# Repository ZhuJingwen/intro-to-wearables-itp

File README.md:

# intro-to-wearables-itp
A repository of examples for the class Intro to Wearables.

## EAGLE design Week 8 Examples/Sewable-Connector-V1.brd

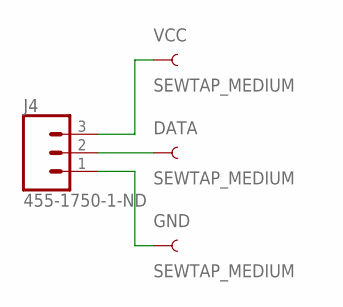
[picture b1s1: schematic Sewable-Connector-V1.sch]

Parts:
DATA: SEWTAP_MEDIUM; PETAL-MEDIUM
GND: SEWTAP_MEDIUM; PETAL-MEDIUM
J4: 455-1750-1-ND; 1X03
VCC: SEWTAP_MEDIUM; PETAL-MEDIUM

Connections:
unnamed: J4.3, VCC.1
unnamed: DATA.1, J4.2
unnamed: GND.1, J4.1

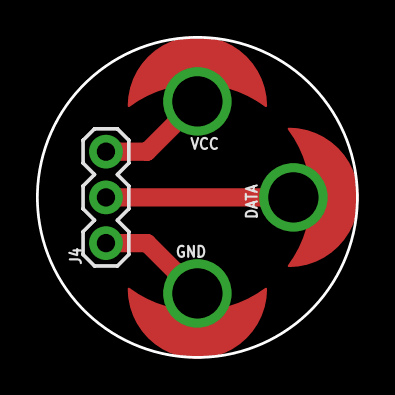
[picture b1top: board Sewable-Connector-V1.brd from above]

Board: 2 copper layers, 17.8 x 17.8 mm, 4 parts (0 on the bottom side), 3 nets.

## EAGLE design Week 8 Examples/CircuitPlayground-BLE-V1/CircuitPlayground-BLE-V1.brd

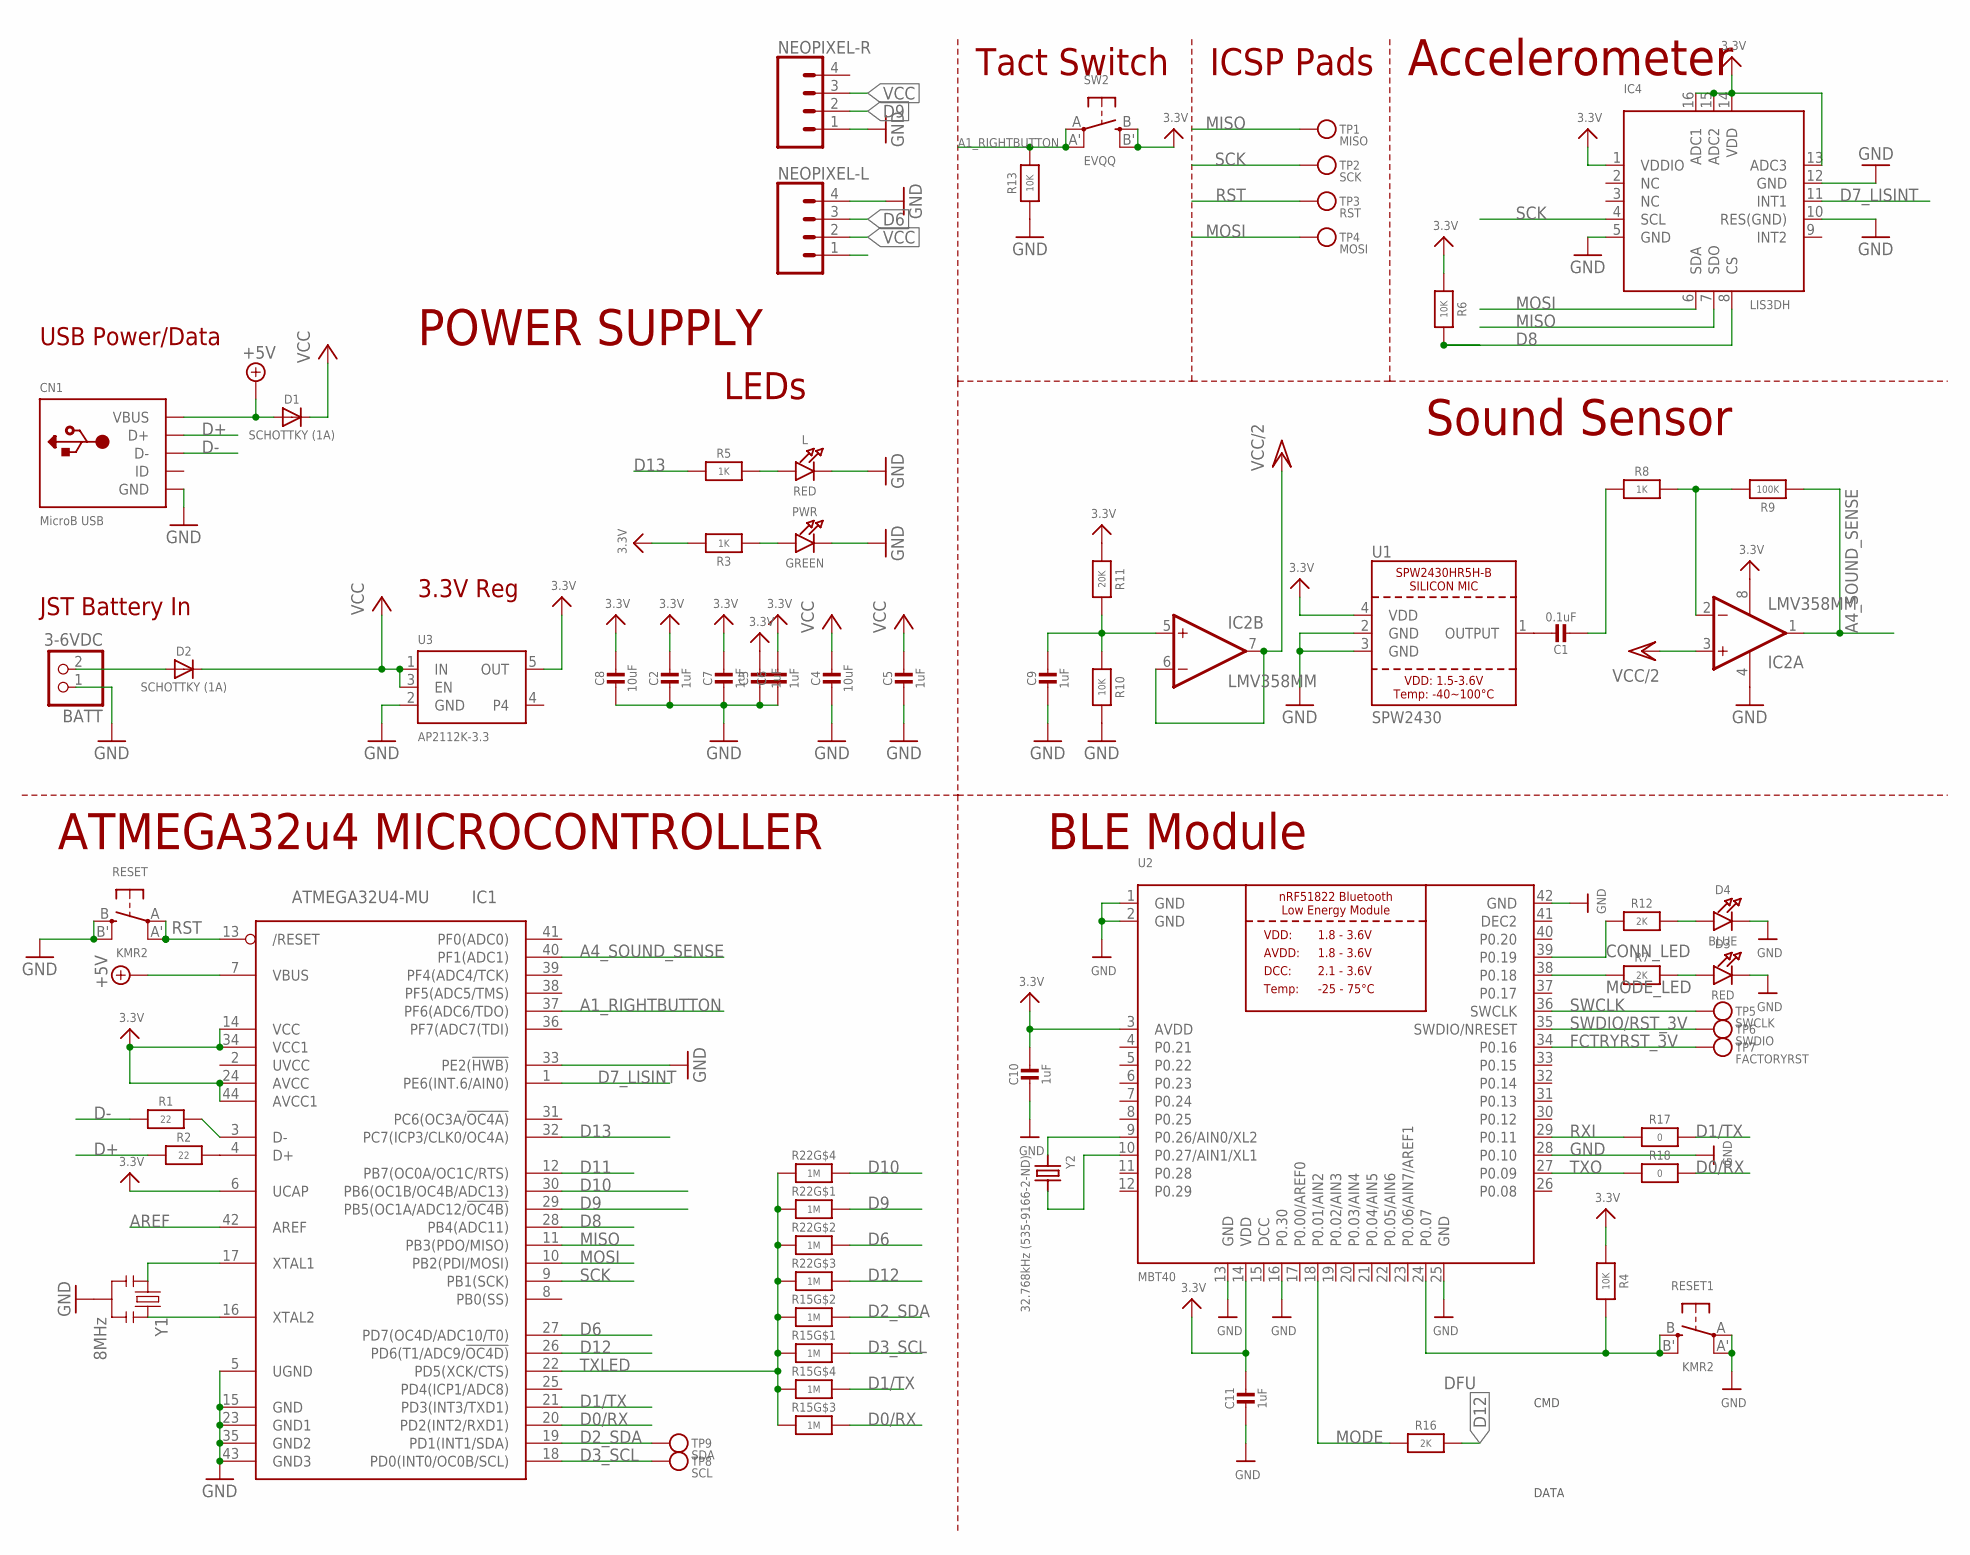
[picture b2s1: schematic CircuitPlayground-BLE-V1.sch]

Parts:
BATT: 3-6VDC; JSTPH2
C1: 0.1uF; 0603-NO
C2, C3, C5, C6, C7, C9: 1uF; 0603-NO
C4, C8: 10uF; 0805-NO
C10, C11: 1uF; 0805-NO
CN1: MicroB USB; 4UCONN_20329_V2
D1, D2: SCHOTTKY (1A); SOD-123
D3: RED; CHIPLED_0805_NOOUTLINE
D4: BLUE; CHIPLED_0805_NOOUTLINE
IC1: ATMEGA32U4-MU; TQFN44_7MM
IC2: LMV358MM; MSOP08
IC4: LIS3DH; LGA16_3X3MM
L: RED; CHIPLED_0805_NOOUTLINE
NEOPIXEL-L: CONN_04; 1X04
NEOPIXEL-R: CONN_04; 1X04
PWR: GREEN; CHIPLED_0805_NOOUTLINE
R1, R2: 22; 0603-NO
R3, R5, R8: 1K; 0603-NO
R4: 10K; 0805-NO
R6, R10, R13: 10K; 0603-NO
R7, R12, R16: 2K; 0805-NO
R9: 100K; 0603-NO
R11: 20K; 0603-NO
R15, R22: 1M; RESPACK_4X0603_NO
R17, R18: 0; 0603-NO
RESET, RESET1: KMR2; BTN_KMR2_4.6X2.8
SW2: EVQQ; EVQ-Q2_SMALLER
TP1: MISO; TESTPOINT_ROUND_1.5MM
TP2: SCK; TESTPOINT_ROUND_1.5MM
TP3: RST; TESTPOINT_ROUND_1.5MM
TP4: MOSI; TESTPOINT_ROUND_1.5MM
TP5: SWCLK; TESTPOINT_ROUND_1.5MM
TP6: SWDIO; TESTPOINT_ROUND_1.5MM
TP7: FACTORYRST; TESTPOINT_ROUND_1.5MM
TP8: SCL; TESTPOINT_ROUND_1.5MM
TP9: SDA; TESTPOINT_ROUND_1.5MM
U1: SPW2430; SPW2430HR5H-B
U2: MBT40; BLE_MODULE_RAYTAC_MDBT40
U3: AP2112K-3.3; SOT23-5
Y1: 8MHz; RESONATOR-SMD
Y2: 32.768kHz (535-9166-2-ND); CRYSTAL_CYL_2X6MM_SMT

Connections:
3.3V: C2.1, C3.1, C6.1, C7.1, C8.1, C10.1, C11.1, IC1.6 (UCAP), IC1.14 (VCC), IC1.24 (AVCC), IC1.34 (VCC1), IC1.44 (AVCC1), IC2.8 (V+), IC4.1 (VDDIO), IC4.13 (ADC3), IC4.14 (VDD), IC4.15 (ADC2), IC4.16 (ADC1), NEOPIXEL-L.1, R3.2, R4.1, R6.1, R11.1, SW2.B (S), SW2.B' (S1), U1.4 (VDD), U2.3 (AVDD), U2.14 (VDD), U3.5 (OUT)
+5V: CN1.VBUS, D1.A, IC1.7 (VBUS)
A1_RIGHTBUTTON: IC1.37 (PF6(ADC6/TDO)), R13.2, SW2.A, SW2.A' (P1)
A4_SOUND_SENSE: IC1.40 (PF1(ADC1)), IC2.1 (OUT), R9.1
AREF: IC1.42 (AREF)
CONN_LED: R12.1, U2.39 (P0.19)
D0/RX: IC1.20 (PD2(INT2/RXD1)), R15.6 (2), R18.2
D1/TX: IC1.21 (PD3(INT3/TXD1)), R15.5 (2), R17.2
D2_SDA: IC1.19 (PD1(INT1/SDA)), R15.7 (2), TP9.P$1
D3_SCL: IC1.18 (PD0(INT0/OC0B/SCL)), R15.8 (2), TP8.P$1
D6: IC1.27 (PD7(OC4D/ADC10/T0)), NEOPIXEL-L.3, R22.7 (2)
D7_LISINT: IC1.1 (PE6(INT.6/AIN0)), IC4.11 (INT1)
D8: IC1.28 (PB4(ADC11)), IC4.8 (CS), R6.2
D9: IC1.29 (PB5(OC1A/ADC12/!OC4B)), NEOPIXEL-R.2, R22.8 (2)
D10: IC1.30 (PB6(OC1B/OC4B/ADC13)), R22.5 (2)
D11: IC1.12 (PB7(OC0A/OC1C/RTS))
D12: IC1.26 (PD6(T1/ADC9/!OC4D)), R16.2, R22.6 (2)
D13: IC1.32 (PC7(ICP3/CLK0/OC4A)), R5.1
D+: CN1.D+, R2.1
D-: CN1.D-, R1.1
DCC: U2.15 (DCC)
DEC2: U2.41 (DEC2)
DFU: R4.2, RESET1.B (S), RESET1.B' (S1), U2.24 (P0.07)
FCTRYRST_3V: TP7.P$1, U2.34 (P0.16)
GND: BATT.1, C2.2, C3.2, C4.2, C5.2, C6.2, C7.2, C8.2, C9.2, C10.2, C11.2, CN1.BASE@1 (GND), CN1.BASE@2 (GND), CN1.GND, CN1.SPRT@1 (GND), CN1.SPRT@2 (GND), CN1.SPRT@3 (GND), CN1.SPRT@4 (GND), D3.C, D4.C, IC1.5 (UGND), IC1.15 (GND), IC1.23 (GND1), IC1.33 (PE2(!HWB)), IC1.35 (GND2), IC1.43 (GND3), IC2.4 (V-), IC4.5 (GND), IC4.10 (RES(GND)), IC4.12 (GND), L.C, NEOPIXEL-L.4, NEOPIXEL-R.1, PWR.C, R10.2, R13.1, RESET.B (S), RESET.B' (S1), RESET1.A, RESET1.A' (P1), U1.2 (GND), U1.3 (GND), U2.1 (GND), U2.2 (GND), U2.13 (GND), U2.16 (P0.30), U2.25 (GND), U2.28 (P0.10), U2.42 (GND), U3.2 (GND), Y1.2
MISO: IC1.11 (PB3(PDO/MISO)), IC4.7 (SDO), TP1.P$1
MODE: R16.1, U2.18 (P0.01/AIN2)
MODE_LED: R7.1, U2.38 (P0.18)
MOSI: IC1.10 (PB2(PDI/MOSI)), IC4.6 (SDA), TP4.P$1
unnamed: PWR.A, R3.1
unnamed: IC2.2 (-IN), R8.2, R9.2
unnamed: IC1.3 (D-), R1.2
unnamed: IC1.4 (D+), R2.2
unnamed: D3.A, R7.2
unnamed: C9.1, IC2.5 (+IN), R10.1, R11.2
unnamed: BATT.2, D2.A
unnamed: IC1.17 (XTAL1), Y1.1
unnamed: IC1.16 (XTAL2), Y1.3
unnamed: L.A, R5.2
unnamed: D4.A, R12.2
unnamed: U2.9 (P0.26/AIN0/XL2), Y2.1
unnamed: U2.10 (P0.27/AIN1/XL1), Y2.2
unnamed: C1.2, R8.1
RST: IC1.13 (/RESET), RESET.A, RESET.A' (P1), TP3.P$1
RXI: R17.1, U2.29 (P0.11)
SCK: IC1.9 (PB1(SCK)), IC4.4 (SCL), TP2.P$1
SOUNDOUT: C1.1, U1.1 (OUTPUT)
SWCLK: TP5.P$1, U2.36 (SWCLK)
SWDIO/RST_3V: TP6.P$1, U2.35 (SWDIO/NRESET)
TXLED: IC1.22 (PD5(XCK/CTS)), R15.1, R15.2 (1), R15.3 (1), R15.4 (1), R22.1, R22.2 (1), R22.3 (1), R22.4 (1)
TXO: R18.1, U2.27 (P0.09)
VCC: C4.1, C5.1, D1.C, D2.C, NEOPIXEL-L.2, NEOPIXEL-R.3, U3.1 (IN), U3.3 (EN)
VCC/2: IC2.3 (+IN), IC2.6 (-IN), IC2.7 (OUT)

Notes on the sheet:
ATMEGA32u4 MICROCONTROLLER
USB Power/Data
JST Battery In
3.3V Reg
POWER SUPPLY
Sound Sensor
Tact Switch
LEDs
ICSP Pads
Accelerometer
DATA
CMD
BLE Module

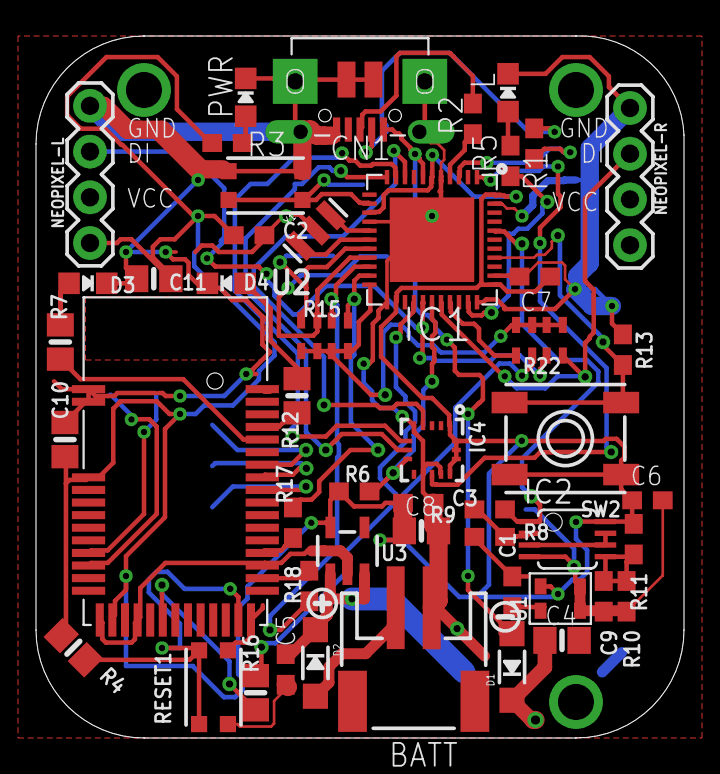
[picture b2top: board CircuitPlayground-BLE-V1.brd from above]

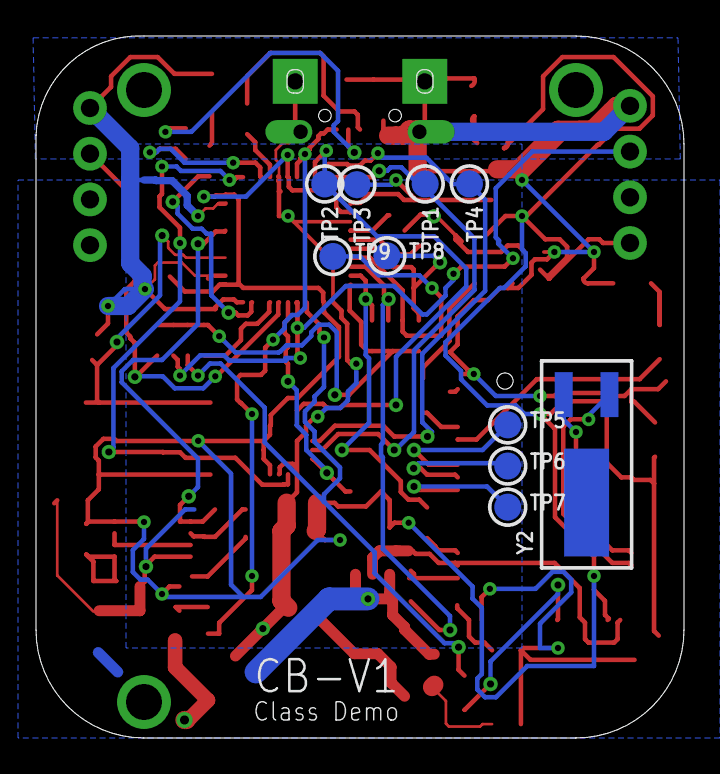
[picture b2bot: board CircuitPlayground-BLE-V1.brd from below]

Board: 2 copper layers, 36.0 x 39.0 mm, 62 parts (11 on the bottom side), 49 nets.

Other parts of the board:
U$1: SYMBOL_MINUS
U$35: SYMBOL_PLUS
U$46: CPLAYBACK

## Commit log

2019-02-17 init
2019-03-31 create arduino-mkrwifi1010-firmware-update
2019-03-31 update the tutorial
2019-03-31 added week 7 examples
2019-03-31 added gitignore
2019-04-01 added examples
2019-04-05 added week 8 contents
2020-03-06 added neopixel examples
2020-03-10 added accelerometer example
2020-03-10 changed file name
2020-03-10 .DS_Store banished!

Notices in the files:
parts and their libraries:
microbuilder: This work is placed in the public domain, and may be freely used for commercial and non-commercial work with the following conditions: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
SparkFun: Licensing: CC v3.0 Share-Alike You are welcome to use this library for commercial purposes.
